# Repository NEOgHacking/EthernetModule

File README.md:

# EthernetModule
This is a custom Ethernet module for the hackxpansion console made by @koeg. It has been created with some simple components. It was made for the purpose of having internet on the hackxpansion console via wire, or even to have local multiplayer.

## Design
This module has been designed with the following requirements and components
single slot hackxpansion module
W5500 PHY ic communicating over spi
Ethernet port with integrated magnetics
length and impedance matched
up to 100Mb/s speed

## Schematic

## PCB

## Case

https://cad.onshape.com/documents/23acd3255b900cc5b85fa1fc/w/7ef244823df79fb773706f50/e/06be5b5812756bedfbe98cc1?renderMode=0&uiState=6abc17ba1a93f5edf6ffc618

## Code
I used the tutorial on the first driver heavily when writing the code for this module.

## BOM

| Place | Cost |
| --- | --- |
| LCSC | $38.34 |
| JLCPCB | $11.62 |
| Total | $49.96 |

# Credits
# **@KOEG**

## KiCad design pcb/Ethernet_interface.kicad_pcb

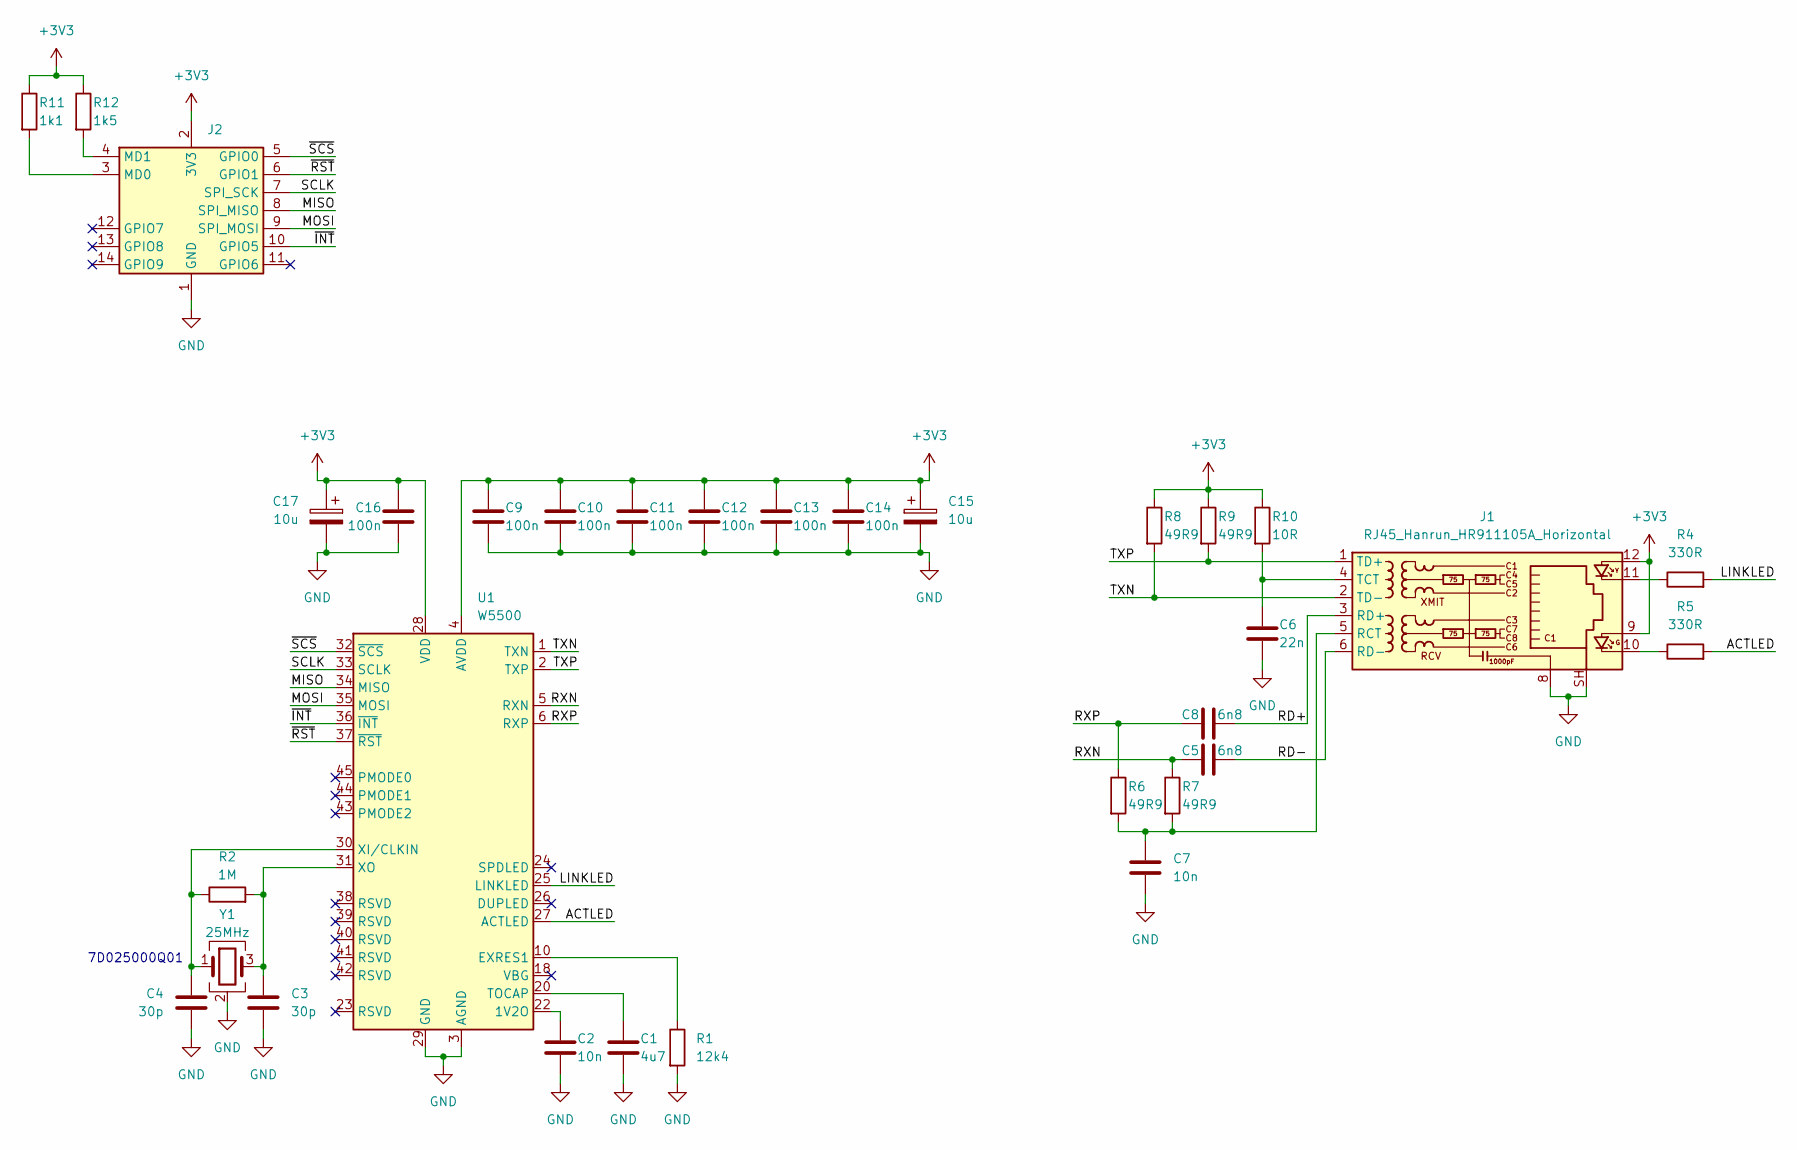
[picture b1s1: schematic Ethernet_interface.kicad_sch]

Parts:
C1: 4u7; C_0603_1608Metric; LCSC C1705
C2, C7: 10n; C_0402_1005Metric; LCSC C15195
C3, C4: 30p; C_0402_1005Metric; LCSC C2186903
C5, C8: 6n8; C_0402_1005Metric; LCSC C318580
C6: 22n; C_0402_1005Metric; LCSC C337699
C9, C10, C11, C12, C13, C14, C16: 100n; C_0402_1005Metric; LCSC C1525
C15, C17: 10u; C_0805_2012Metric; LCSC C1969735
J1: RJ45_Hanrun_HR911105A_Horizontal; LCSC C12074
J2: PinHeader_2x07_P2.54mm_Horizontal
R1: 12k4; R_0402_1005Metric; LCSC C138060
R2: 1M; R_0402_1005Metric; LCSC C138033
R4, R5: 330R; R_0402_1005Metric; LCSC C105875
R6, R7, R8, R9: 49R9; R_0402_1005Metric; LCSC C87044
R10: 10R; R_0402_1005Metric; LCSC C138066
R11: 1k1; R_0402_1005Metric; LCSC C2909306
R12: 1k5; R_0402_1005Metric; LCSC C114759
U1: W5500; LQFP-48_7x7mm_P0.5mm; LCSC C32843
Y1: 25MHz; Crystal_SMD_2016-4Pin_2.0x1.6mm; LCSC C648942

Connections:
+3V3: C9.1, C10.1, C11.1, C12.1, C13.1, C14.1, C15.1, C16.1, C17.1, J1.9, J1.12, J2.2 (3V3), R8.1, R9.1, R10.1, R11.1, R12.1, U1.4 (AVDD), U1.8 (AVDD), U1.11 (AVDD), U1.15 (AVDD), U1.17 (AVDD), U1.21 (AVDD), U1.28 (VDD)
/ACTLED: R5.2, U1.27 (ACTLED)
/LINKLED: R4.2, U1.25 (LINKLED)
/MISO: J2.8 (SPI_MISO), U1.34 (MISO)
/MOSI: J2.9 (SPI_MOSI), U1.35 (MOSI)
/RD+: C8.2, J1.3 (RD+)
/RD-: C5.2, J1.6 (RD-)
/RXN: C5.1, R7.1, U1.5 (RXN)
/RXP: C8.1, R6.1, U1.6 (RXP)
/SCLK: J2.7 (SPI_SCK), U1.33 (SCLK)
/TXN: J1.2 (TD-), R8.2, U1.1 (TXN)
/TXP: J1.1 (TD+), R9.2, U1.2 (TXP)
/~INT: J2.10 (GPIO5), U1.36 (~INT)
/~RST: J2.6 (GPIO1), U1.37 (~RST)
/~SCS: J2.5 (GPIO0), U1.32 (~SCS)
GND: C1.2, C2.2, C3.2, C4.2, C6.2, C7.2, C9.2, C10.2, C11.2, C12.2, C13.2, C14.2, C15.2, C16.2, C17.2, J1.8, J1.SH, J2.1 (GND), R1.2, U1.3 (AGND), U1.9 (AGND), U1.14 (AGND), U1.16 (AGND), U1.19 (AGND), U1.29 (GND), U1.48 (AGND), Y1.2 (G), Y1.4 (G)
unnamed: J1.10, R5.1
unnamed: J1.11, R4.1
unnamed: C7.1, J1.5 (RCT), R6.2, R7.2
unnamed: C6.1, J1.4 (TCT), R10.2
unnamed: J2.3 (MD0), R11.2
unnamed: J2.4 (MD1), R12.2
unnamed: C2.1, U1.22 (1V2O)
unnamed: R1.1, U1.10 (EXRES1)
unnamed: C1.1, U1.20 (TOCAP)
unnamed: C4.1, R2.1, U1.30 (XI/CLKIN), Y1.1
unnamed: C3.1, R2.2, U1.31 (XO), Y1.3

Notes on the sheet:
7D025000Q01

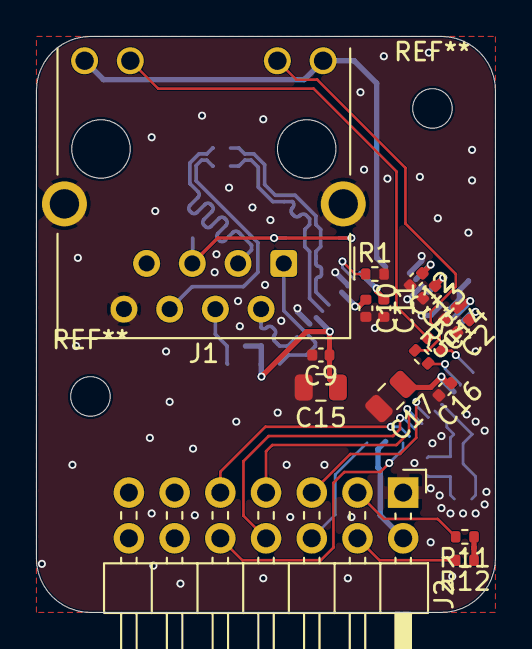
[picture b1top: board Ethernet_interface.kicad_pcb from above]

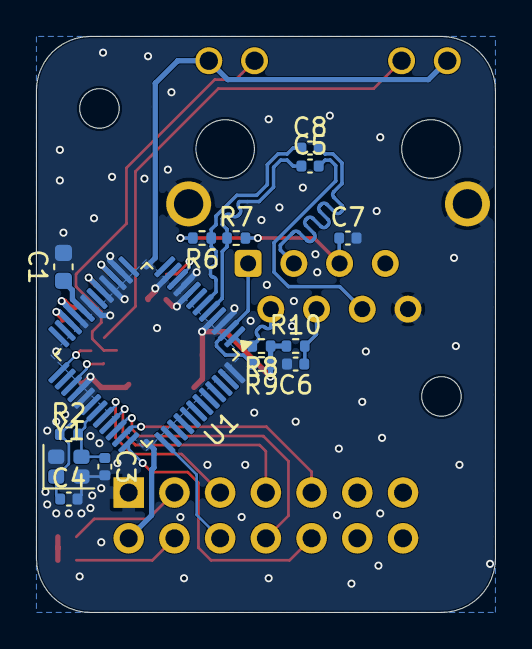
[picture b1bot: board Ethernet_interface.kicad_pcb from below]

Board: 2 copper layers, 25.5 x 32.0 mm, 32 parts (15 on the bottom side), 27 nets.

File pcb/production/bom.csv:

Designator,Footprint,Quantity,Value,LCSC Part #
C1,0603,1,4u7,
"C10, C11, C12, C13, C14, C16, C9",0402,7,100n,
"C15, C17",0805,2,10u,C1969735
"C2, C7",0402,2,10n,
"C3, C4",0402,2,30p,
"C5, C8",0402,2,6n8,
C6,0402,1,22n,
J1,RJ45_Hanrun_HR911105A_Horizontal,1,RJ45_Hanrun_HR911105A_Horizontal,C12074
J2,PinHeader_2x07_P2.54mm_Horizontal,1,~,
R1,0402,1,12k4,
R10,0402,1,10R,
R11,0402,1,1k1,
R12,0402,1,1k5,
R2,0402,1,1M,
"R4, R5",0402,2,330R,
"R6, R7, R8, R9",0402,4,49R9,
U1,LQFP-48_7x7mm_P0.5mm,1,W5500,C32843
Y1,Crystal_SMD_2016-4Pin_2.0x1.6mm,1,25MHz,C648942
